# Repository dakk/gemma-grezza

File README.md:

# Gemma Grezza - My UncutGem build

These are my edits, files and notes from my attempt to build UncutGem from Quantum Village, a Full Stack fully Open Source NV Center Diamond Magnetometer. If you want to build one, go to [Quantum Village website](https://quantumvillage.org/#test-site-intro-md) and [UncutGem github](https://github.com/QuantumVillage/UncutGem/).

## What I've done differently
- used a [custom mold](./mold) for casting the diamond 
- created a [3d printable enclosure](./model)
- build a [pcb in Kicad](./pcb)
- made some modifications to the [firmware](./firmware)
- added a button to interact with the device

## Firmware

The firmware is a custom modification of the original; in particular # TODO

## Build process & results

The build process is told in this blogpost: # TODO

## Licensing

This project is under the [Affero GPL license](./LICENSE) as the original UncutGem project. This is a paritcularly restrictive license that demands any and all updates from anyone using this project. The AGPL is designed specifically to ensure that any modified material becomes available to the community. Specifically:

> Notwithstanding any other provision of this License, if you modify the Program, your modified version must prominently offer all users interacting with it remotely through a computer network (if your version supports such interaction) an opportunity to receive the Corresponding Source of your version by providing access to the Corresponding Source from a network server at no charge, through some standard or customary means of facilitating copying of software. [...]

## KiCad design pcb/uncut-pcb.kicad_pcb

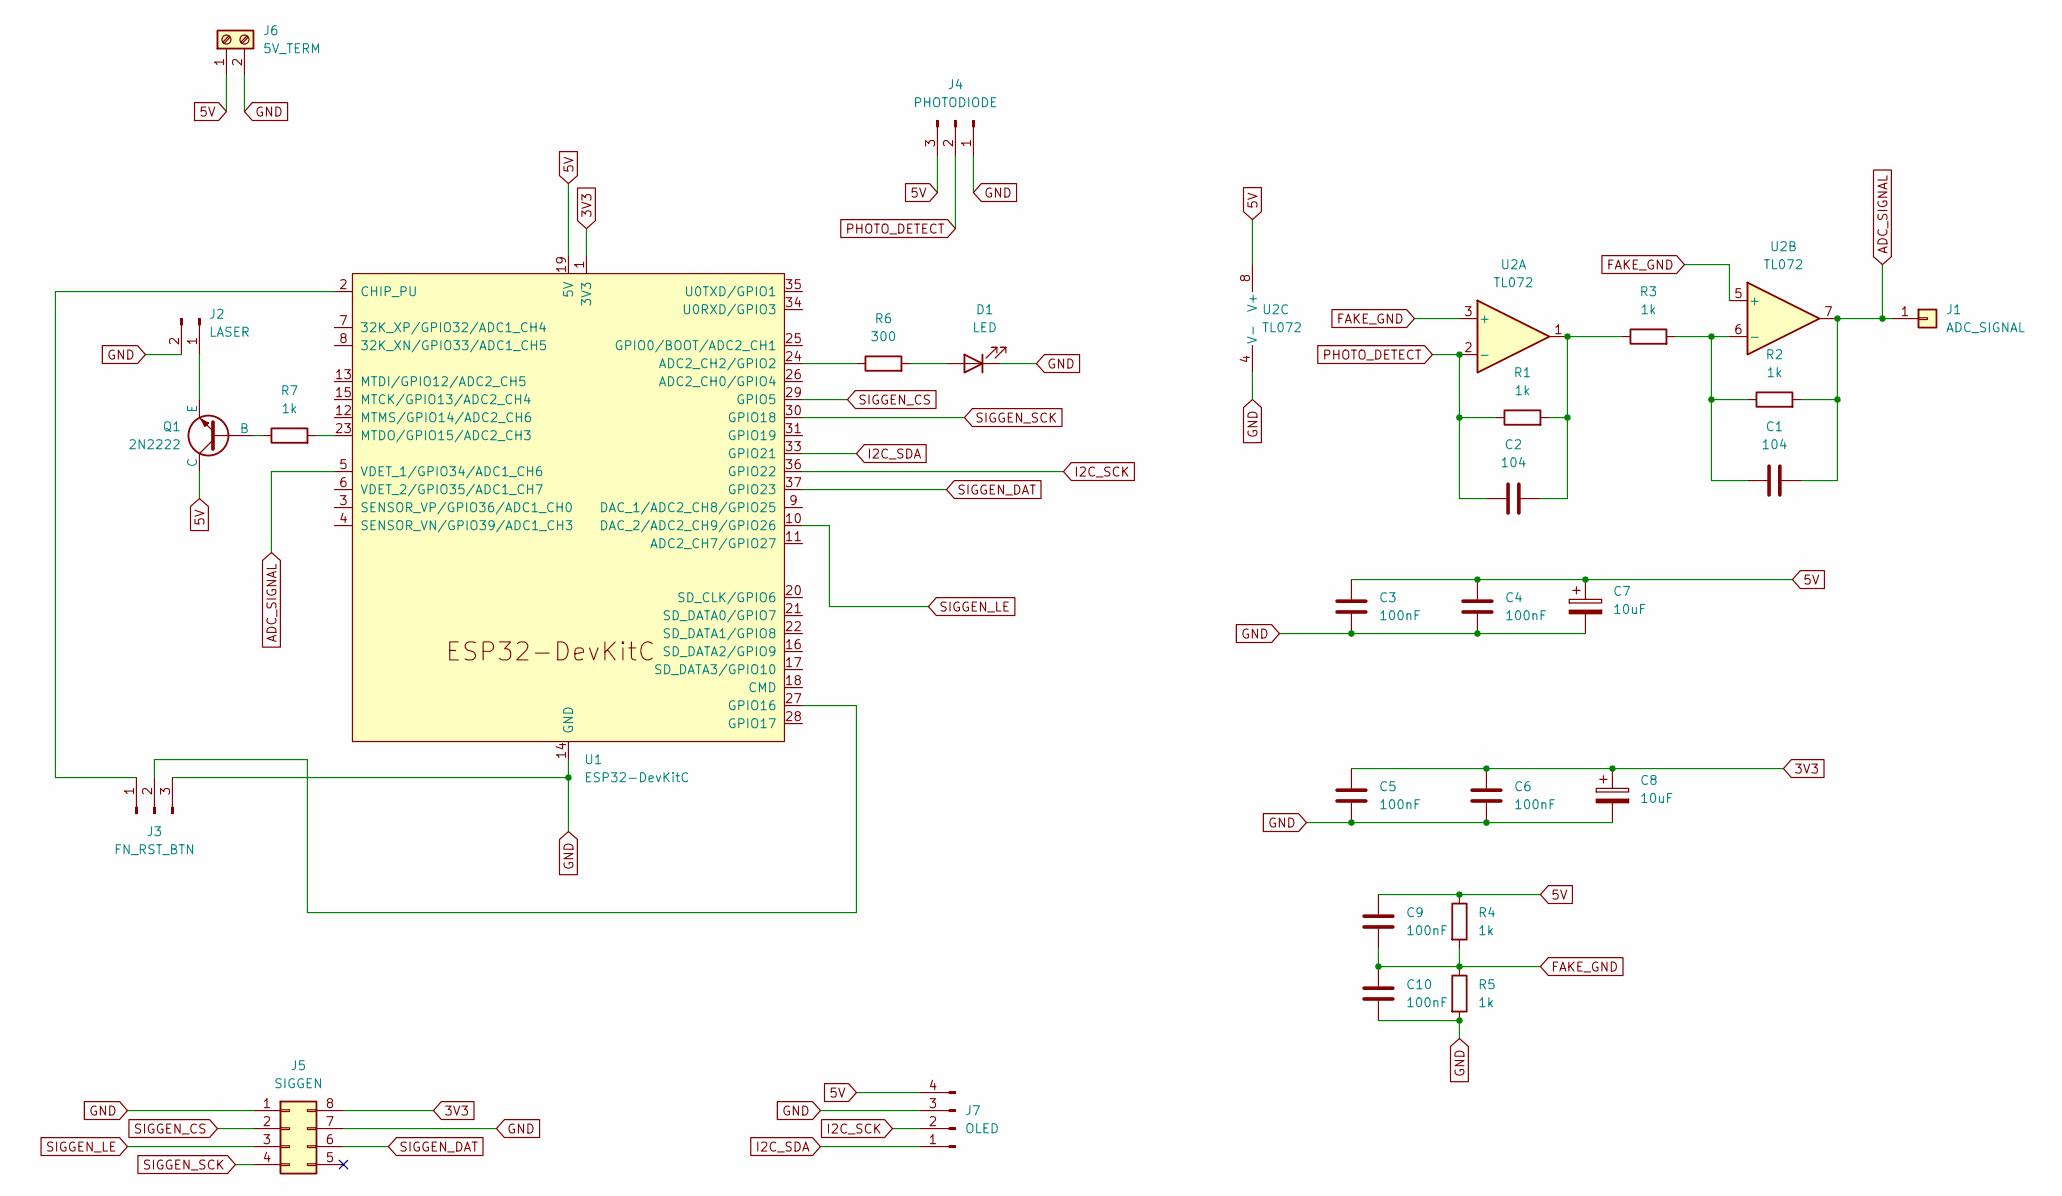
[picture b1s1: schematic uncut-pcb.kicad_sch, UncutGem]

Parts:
C1, C2: 104; C_Disc_D7.5mm_W2.5mm_P5.00mm
C3, C4, C5, C6, C9, C10: 100nF; C_Disc_D7.5mm_W2.5mm_P5.00mm
C7, C8: 10uF; CP_Radial_D4.0mm_P2.00mm
D1: LED; LED_D3.0mm
J1: ADC_SIGNAL; PinHeader_1x01_P1.00mm_Vertical
J2: LASER; JST_EH_B2B-EH-A_1x02_P2.50mm_Vertical
J3: FN_RST_BTN; JST_EH_B3B-EH-A_1x03_P2.50mm_Vertical
J4: PHOTODIODE; JST_EH_B3B-EH-A_1x03_P2.50mm_Vertical
J5: SIGGEN; PinHeader_2x04_P2.54mm_Vertical
J6: 5V_TERM; JST_EH_B2B-EH-A_1x02_P2.50mm_Vertical
J7: OLED; JST_EH_B4B-EH-A_1x04_P2.50mm_Vertical
Q1: 2N2222; TO-92
R1, R2, R3, R4, R5, R7: 1k; R_Axial_DIN0204_L3.6mm_D1.6mm_P7.62mm_Horizontal
R6: 300; R_Axial_DIN0204_L3.6mm_D1.6mm_P7.62mm_Horizontal
U1: ESP32-DevKitC
U2: TL072; DIP-8_W7.62mm

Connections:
3V3: C5.1, C6.1, C8.1, J5.8, U1.1 (3V3)
5V: C3.1, C4.1, C7.1, C9.1, J4.3, J6.1, J7.4, Q1.1 (C), R4.1, U1.19 (5V), U2.8 (V+)
ADC_SIGNAL: C1.2, J1.1, R2.2, U1.5 (VDET_1/GPIO34/ADC1_CH6), U2.7
FAKE_GND: C9.2, C10.1, R4.2, R5.1, U2.3 (+), U2.5 (+)
GND: C3.2, C4.2, C5.2, C6.2, C7.2, C8.2, C10.2, D1.1 (K), J2.2, J3.3, J4.1, J5.1, J5.7, J6.2, J7.3, R5.2, U1.14 (GND), U1.32 (GND), U1.38 (GND), U2.4 (V-)
I2C_SCK: J7.2, U1.36 (GPIO22)
I2C_SDA: J7.1, U1.33 (GPIO21)
unnamed: C2.2, R1.2, R3.1, U2.1
unnamed: D1.2 (A), R6.2
unnamed: J2.1, Q1.3 (E)
unnamed: J3.1, U1.2 (CHIP_PU)
unnamed: J3.2, U1.27 (GPIO16)
unnamed: Q1.2 (B), R7.1
unnamed: R6.1, U1.24 (ADC2_CH2/GPIO2)
unnamed: R7.2, U1.23 (MTDO/GPIO15/ADC2_CH3)
unnamed: C1.1, R2.1, R3.2, U2.6 (-)
PHOTO_DETECT: C2.1, J4.2, R1.1, U2.2 (-)
SIGGEN_CS: J5.2, U1.29 (GPIO5)
SIGGEN_DAT: J5.6, U1.37 (GPIO23)
SIGGEN_LE: J5.3, U1.10 (DAC_2/ADC2_CH9/GPIO26)
SIGGEN_SCK: J5.4, U1.30 (GPIO18)

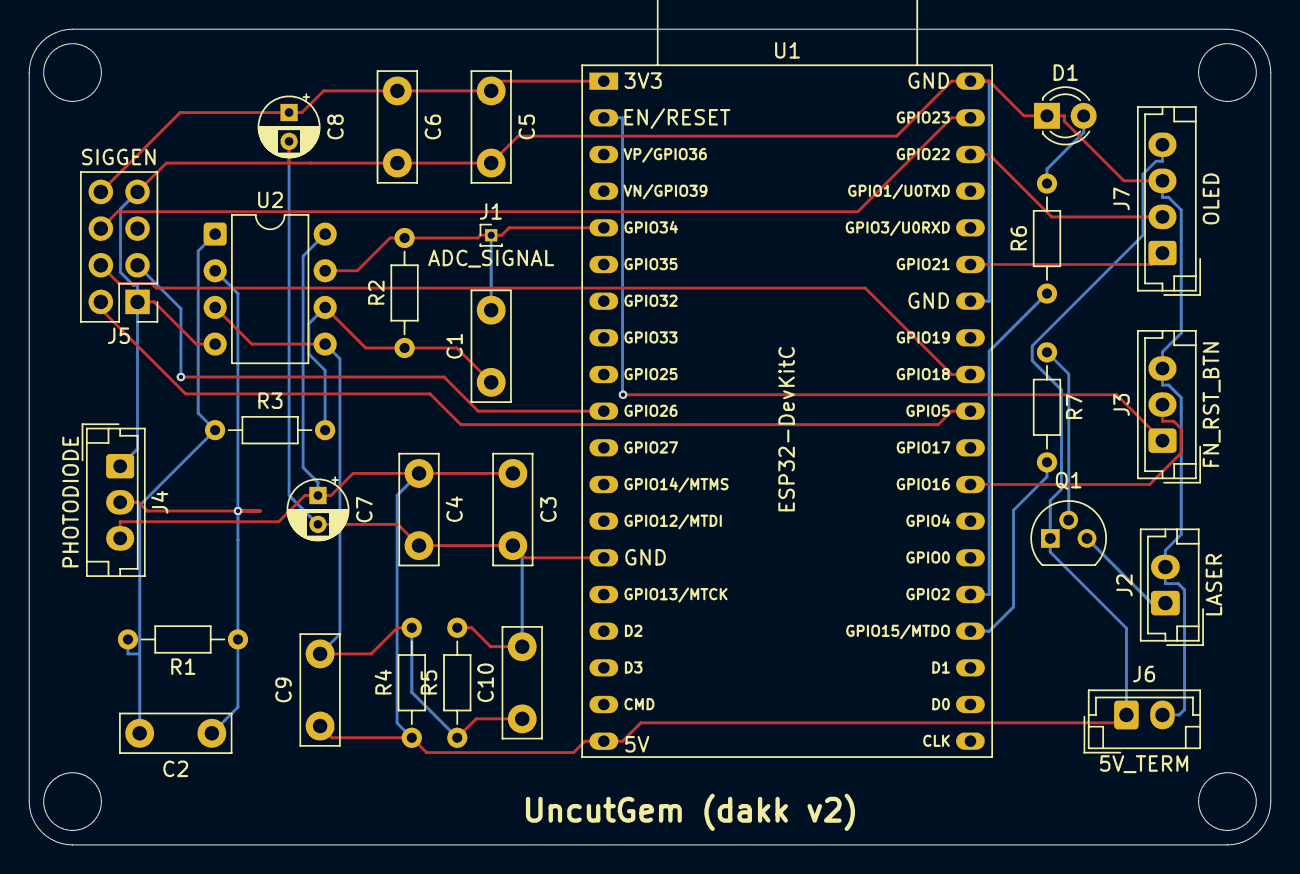
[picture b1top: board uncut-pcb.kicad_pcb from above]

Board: 2 copper layers, 86.0 x 56.5 mm, 28 parts (0 on the bottom side), 21 nets.

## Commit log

2025-11-06 pcb and models
2025-11-06 pcb update
2025-11-07 firmware
